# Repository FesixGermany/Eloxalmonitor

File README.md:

# Eloxalmonitor  

This project started some years back when I started anodizing some aluminium at home.  
The temperature of the bath is very critical, when it gets too high the developed oxide pores start to destroy themselfes.  
That's why I wanted to read at least the temperature, voltage and current would be nice to know too.  

My friend Sven Mueller (who sadly passed away in 2018 just shy of 24 years old) wrote parts of the code, mainly the functions for onewire communication and decoding of the temperature back in 2017.  
I forgot about the project but now got into it again and finished it as good as I could by myself.  

## Circuit  

The brain is an Arduino Nano clone, convenient to use for serial communication with UART to USB converter on board.  
The main PCB plugs directly into my lab power supply, voltage gets read via voltage divider up to 30V DC, current is read via a 0R1 shunt resistor.  
Temperature of two basins can be read with two DS18B20 sensors who can be bought with cable attached and stainless steel cap.  

## Firmware 

The firmware for the ATmega 328P controller on the Nano is written in ATMEL Studio, not in Arduino IDE, therefore the controller was programmed with the .hex file which was compiled from ATMEL Studio via a AVR ISP programmer.
As far as I know it is possible to send the compiled .hex to an Arduino over USB with the bootloader installed and the program avrdude but didn't try that.  
**Important to note:** If compiling code yourself it is neccessary to add **libprintf_flt** to linker libraries and **use vprintf** library is set!

## Python GUI  

Script draws four graphs in realtime and stores them in a CSV file.  

Tested with/dependencies:  
python 2.7  
pyserial 3.5  
matplotlib 2.2.5  
numpy 1.16.0  

This is the first script I wrote in python, took some time to figure out how, I'm sure there are better ways but it works for me.

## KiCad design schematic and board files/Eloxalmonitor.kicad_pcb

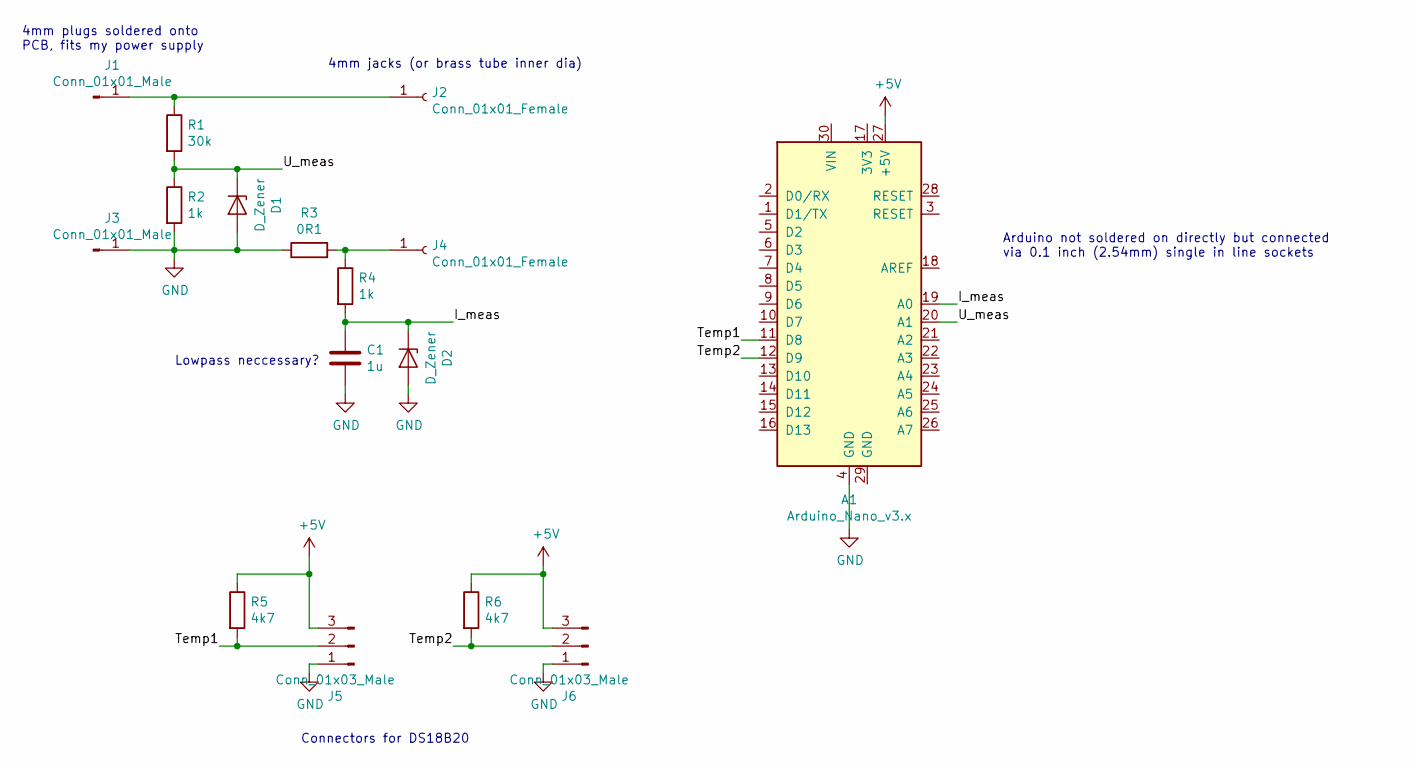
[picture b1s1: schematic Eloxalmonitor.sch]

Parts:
A1: Arduino_Nano_v3.x; Arduino_Nano
C1: 1u; C_0805_2012Metric_Pad1.15x1.40mm_HandSolder
D1, D2: D_Zener; D_SOT-23_ANK
J1, J3: Conn_01x01_Male; SolderWirePad_1x01_SMD_5x10mm
J2, J4: Conn_01x01_Female; SolderWirePad_1x01_SMD_5x10mm
J5, J6: Conn_01x03_Male; Molex_KK-254_AE-6410-03A_1x03_P2.54mm_Vertical
R1: 30k; R_0805_2012Metric_Pad1.15x1.40mm_HandSolder
R2, R4: 1k; R_0805_2012Metric_Pad1.15x1.40mm_HandSolder
R3: 0R1; R_2512_6332Metric_Pad1.52x3.35mm_HandSolder
R5, R6: 4k7; R_0805_2012Metric_Pad1.15x1.40mm_HandSolder

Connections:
+5V: A1.27 (+5V), J5.3, J6.3, R5.1, R6.1
/I_meas: A1.19 (A0), C1.1, D2.1 (K), R4.2
/Temp1: A1.11 (D8), J5.2, R5.2
/Temp2: A1.12 (D9), J6.2, R6.2
/U_meas: A1.20 (A1), D1.1 (K), R1.2, R2.1
GND: A1.4 (GND), C1.2, D1.2 (A), D2.2 (A), J3.1, J5.1, J6.1, R2.2, R3.1
unnamed: J1.1, J2.1, R1.1
unnamed: J4.1, R3.2, R4.1

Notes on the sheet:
Connectors for DS18B20
Lowpass neccessary?
Arduino not soldered on directly but connected via 0.1 inch (2.54mm) single in line sockets
4mm plugs soldered onto PCB, fits my power supply
4mm jacks (or brass tube inner dia)

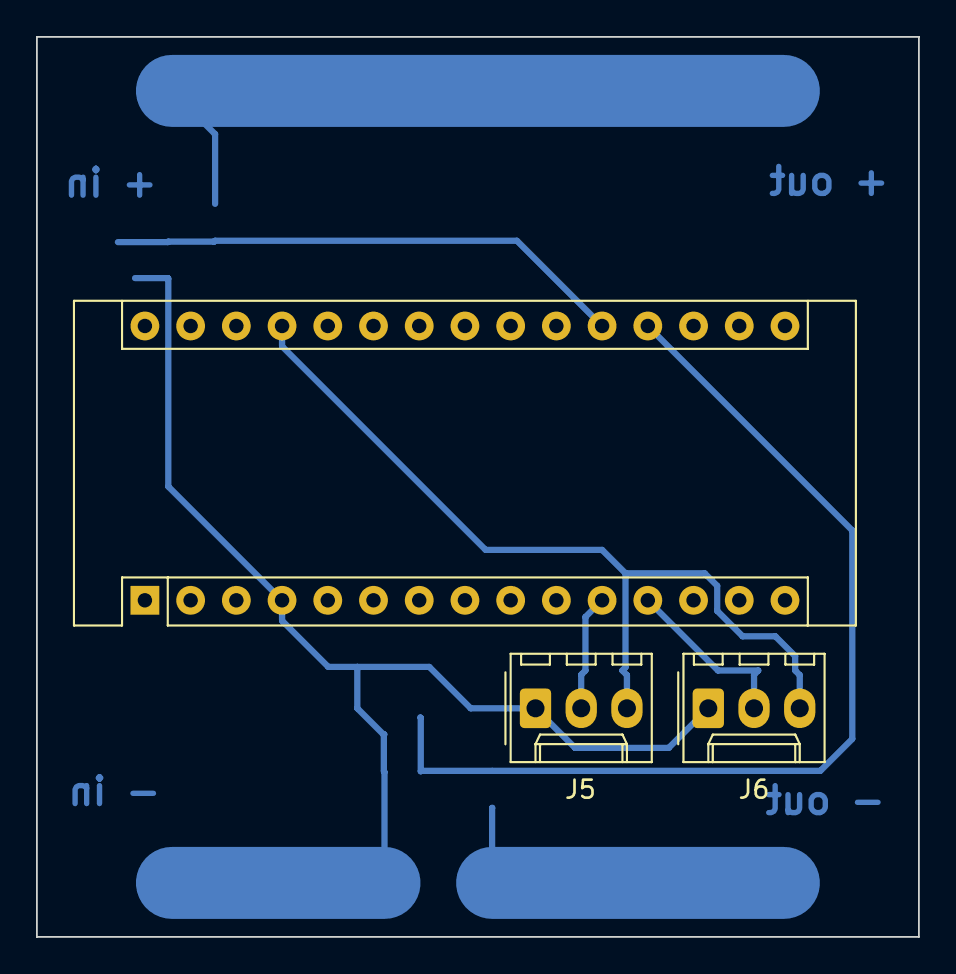
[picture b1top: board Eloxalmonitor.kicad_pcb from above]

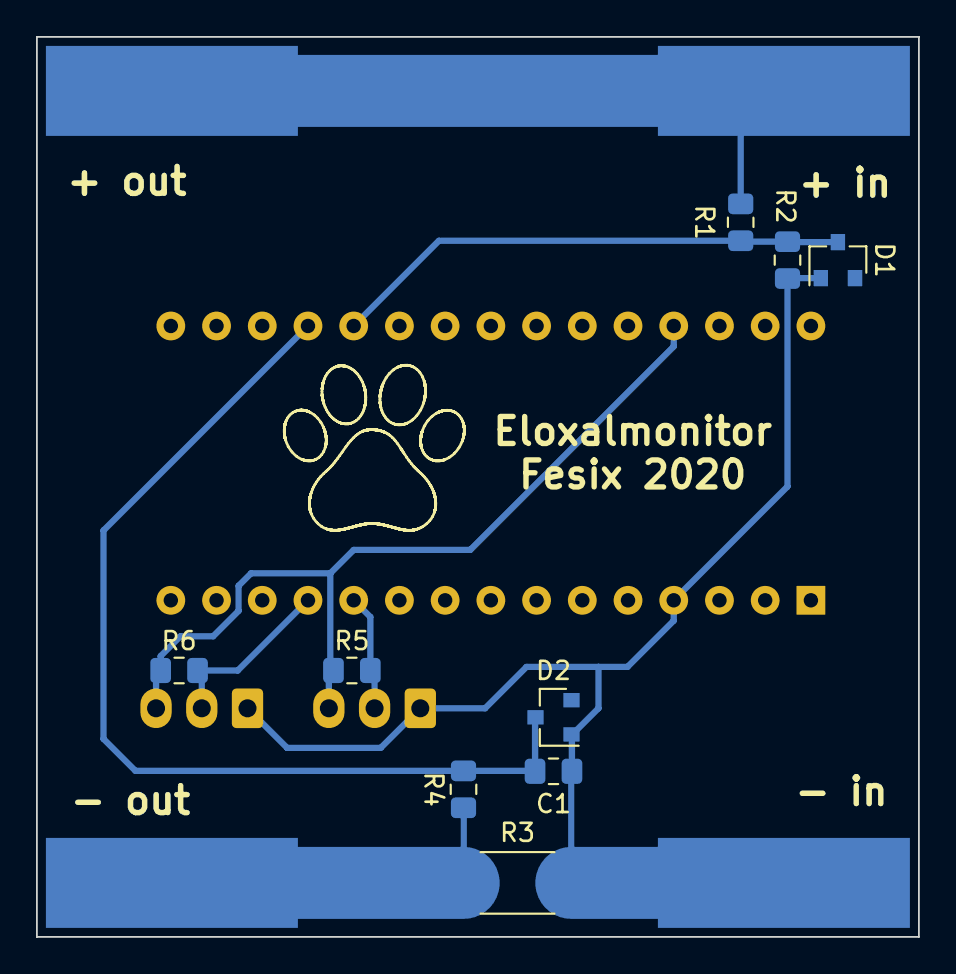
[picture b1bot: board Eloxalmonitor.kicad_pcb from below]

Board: 2 copper layers, 49.0 x 50.0 mm, 16 parts (13 on the bottom side), 8 nets.

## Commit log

2020-12-26 Initial
2021-03-05 Swapped voltage and current label in csv
2021-09-22 Change for use with python 3
